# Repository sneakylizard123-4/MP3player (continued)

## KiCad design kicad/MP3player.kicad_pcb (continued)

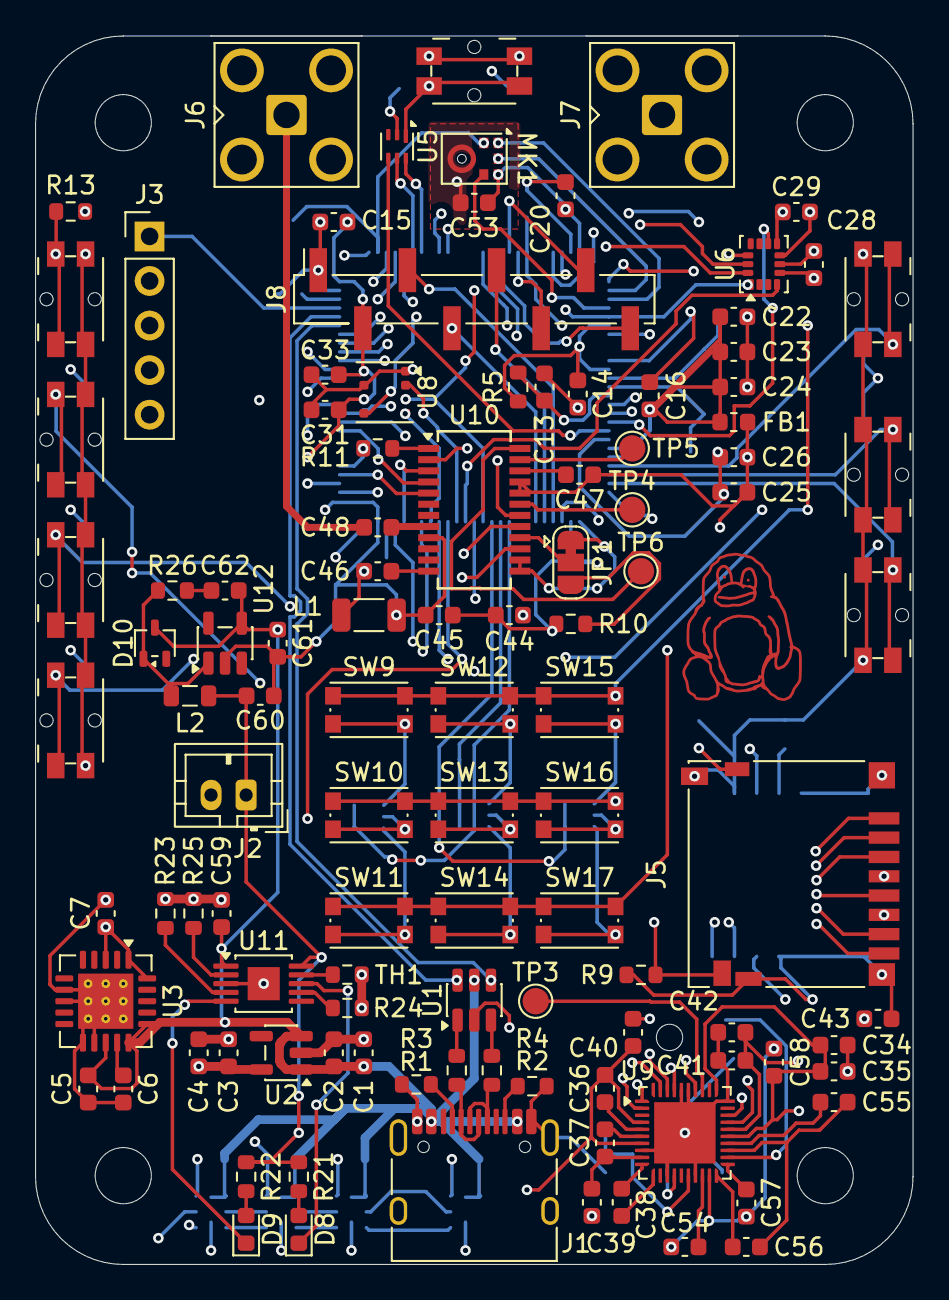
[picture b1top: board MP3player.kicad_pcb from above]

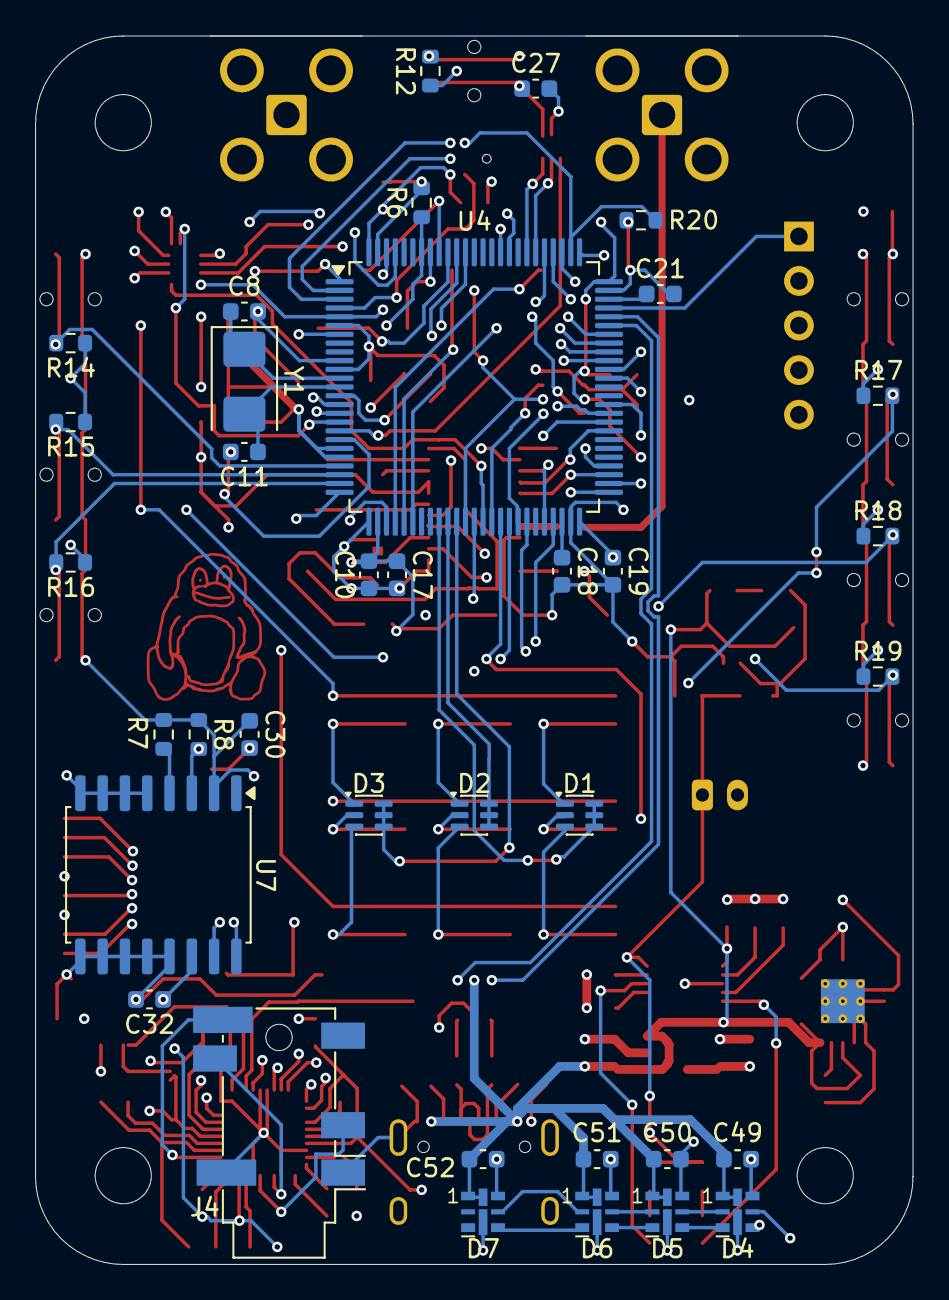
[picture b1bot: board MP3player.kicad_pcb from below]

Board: 6 copper layers, 50.0 x 70.0 mm, 148 parts (36 on the bottom side), 136 nets.

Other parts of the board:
C59: 1uF; C_0603_1608Metric
C60: 4.7uF; C_0603_1608Metric
C61: 22uF; C_0603_1608Metric
C62: 120pF; C_0603_1608Metric
D8, D9: LED; LED_0603_1608Metric
D10: BAT54W; SOT-323_SC-70
L2: 2.2uH; L_0805_2012Metric
R21, R22: 1.5k; R_0603_1608Metric
R23, R25: 1.1k; R_0603_1608Metric
R24: 11k; R_0603_1608Metric
R26: 5.11R; R_0603_1608Metric
TH1: 10k; R_0603_1608Metric
U11: BQ24090DGQ; HVSSOP-10-1EP_3x3mm_P0.5mm_EP1.83x1.89mm
U12: TPS613222ADBV; SOT-23-5

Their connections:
+5V: C59.1, C61.1, C62.2, D10.3 (K), U11.1 (IN), U12.4 (VOUT); also elsewhere on the board
+BATT: C60.1, L2.1, R21.1, R22.1, U11.10 (OUT); also elsewhere on the board
GND: C59.2, C60.2, C61.2, R23.2, R24.2, R25.2, TH1.2, U11.3 (VSS), U11.11 (VSS), U12.2 (GND); also elsewhere on the board
unnamed: C62.1, R26.2
unnamed: D8.2 (A), R21.2
unnamed: D8.1 (K), U11.8 (~CHG)
unnamed: D9.2 (A), R22.2
unnamed: D9.1 (K), U11.5 (~PG)
unnamed: D10.1 (A), L2.2, R26.1, U12.1 (SW)
unnamed: R24.1, U11.7 (ISET2)
unnamed: R25.1, U11.2 (ISET)
unnamed: R23.1, U11.4 (PRETERM)
unnamed: TH1.1, U11.9 (TS)

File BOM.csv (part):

Refs,Value,Footprint,Qty,LCSC#,MPN,Manufacturer,Unit Price($),Product Link
C1,10uF,Capacitor_SMD:C_0603_1608Metric,1,C19702,CL10A106KP8NNNC,Samsung Electro-Mechanics,0.0390,https://www.lcsc.com/product-detail/C19702.html
C2,1uF,Capacitor_SMD:C_0603_1608Metric,1,C29936,CL10B105KA8NNNC,Samsung Electro-Mechanics,0.0229,https://www.lcsc.com/product-detail/C29936.html
C3,10uF,Capacitor_SMD:C_0603_1608Metric,1,C19702,CL10A106KP8NNNC,Samsung Electro-Mechanics,0.0390,https://www.lcsc.com/product-detail/C19702.html
C4,1uF,Capacitor_SMD:C_0603_1608Metric,1,C29936,CL10B105KA8NNNC,Samsung Electro-Mechanics,0.0229,https://www.lcsc.com/product-detail/C29936.html
C5,10uF,Capacitor_SMD:C_0603_1608Metric,1,C19702,CL10A106KP8NNNC,Samsung Electro-Mechanics,0.0390,https://www.lcsc.com/product-detail/C19702.html
C6,1uF,Capacitor_SMD:C_0603_1608Metric,1,C29936,CL10B105KA8NNNC,Samsung Electro-Mechanics,0.0229,https://www.lcsc.com/product-detail/C29936.html
C7,47uF,Capacitor_SMD:C_0603_1608Metric,1,C140782,GRM188R60J476ME15D,muRata,0.2397,https://www.lcsc.com/product-detail/C140782.html
C8,12pF,Capacitor_SMD:C_0603_1608Metric,1,C107034,CC0603JRNPO9BN120,YAGEO,0.0090,https://www.lcsc.com/product-detail/C107034.html
C10,0.1uF,Capacitor_SMD:C_0603_1608Metric,1,C1591,CL10B104KB8NNNC,Samsung Electro-Mechanics,0.0160,https://www.lcsc.com/product-detail/C1591.html
C11,12pF,Capacitor_SMD:C_0603_1608Metric,1,C107034,CC0603JRNPO9BN120,YAGEO,0.0090,https://www.lcsc.com/product-detail/C107034.html
C13,100nF,Capacitor_SMD:C_0603_1608Metric,1,C1591,CL10B104KB8NNNC,Samsung Electro-Mechanics,0.0160,https://www.lcsc.com/product-detail/C1591.html
C14,0.1uF,Capacitor_SMD:C_0603_1608Metric,1,C1591,CL10B104KB8NNNC,Samsung Electro-Mechanics,0.0160,https://www.lcsc.com/product-detail/C1591.html
C15,0.1uF,Capacitor_SMD:C_0603_1608Metric,1,C1591,CL10B104KB8NNNC,Samsung Electro-Mechanics,0.0160,https://www.lcsc.com/product-detail/C1591.html
C16,100nF,Capacitor_SMD:C_0603_1608Metric,1,C1591,CL10B104KB8NNNC,Samsung Electro-Mechanics,0.0160,https://www.lcsc.com/product-detail/C1591.html
C17,0.1uF,Capacitor_SMD:C_0603_1608Metric,1,C1591,CL10B104KB8NNNC,Samsung Electro-Mechanics,0.0160,https://www.lcsc.com/product-detail/C1591.html
C18,2.2uF,Capacitor_SMD:C_0603_1608Metric,1,C23630,CL10A225KO8NNNC,Samsung Electro-Mechanics,0.0289,https://www.lcsc.com/product-detail/C23630.html
C19,100nF,Capacitor_SMD:C_0603_1608Metric,1,C1591,CL10B104KB8NNNC,Samsung Electro-Mechanics,0.0160,https://www.lcsc.com/product-detail/C1591.html
C20,0.1uF,Capacitor_SMD:C_0603_1608Metric,1,C1591,CL10B104KB8NNNC,Samsung Electro-Mechanics,0.0160,https://www.lcsc.com/product-detail/C1591.html
C21,2.2uF,Capacitor_SMD:C_0603_1608Metric,1,C23630,CL10A225KO8NNNC,Samsung Electro-Mechanics,0.0289,https://www.lcsc.com/product-detail/C23630.html
C22,10nF,Capacitor_SMD:C_0603_1608Metric,1,C100042,CC0603KRX7R9BB103,YAGEO,0.0160,https://www.lcsc.com/product-detail/C100042.html
C23,100nF,Capacitor_SMD:C_0603_1608Metric,1,C1591,CL10B104KB8NNNC,Samsung Electro-Mechanics,0.0160,https://www.lcsc.com/product-detail/C1591.html
C24,1uF,Capacitor_SMD:C_0603_1608Metric,1,C29936,CL10B105KA8NNNC,Samsung Electro-Mechanics,0.0229,https://www.lcsc.com/product-detail/C29936.html
C25,1uF,Capacitor_SMD:C_0603_1608Metric,1,C29936,CL10B105KA8NNNC,Samsung Electro-Mechanics,0.0229,https://www.lcsc.com/product-detail/C29936.html
C26,100nF,Capacitor_SMD:C_0603_1608Metric,1,C1591,CL10B104KB8NNNC,Samsung Electro-Mechanics,0.0160,https://www.lcsc.com/product-detail/C1591.html
C27,100nF,Capacitor_SMD:C_0603_1608Metric,1,C1591,CL10B104KB8NNNC,Samsung Electro-Mechanics,0.0160,https://www.lcsc.com/product-detail/C1591.html
C28,100nF,Capacitor_SMD:C_0603_1608Metric,1,C1591,CL10B104KB8NNNC,Samsung Electro-Mechanics,0.0160,https://www.lcsc.com/product-detail/C1591.html
C29,100nF,Capacitor_SMD:C_0603_1608Metric,1,C1591,CL10B104KB8NNNC,Samsung Electro-Mechanics,0.0160,https://www.lcsc.com/product-detail/C1591.html
C30,100nF,Capacitor_SMD:C_0603_1608Metric,1,C1591,CL10B104KB8NNNC,Samsung Electro-Mechanics,0.0160,https://www.lcsc.com/product-detail/C1591.html
C31,100nF,Capacitor_SMD:C_0603_1608Metric,1,C1591,CL10B104KB8NNNC,Samsung Electro-Mechanics,0.0160,https://www.lcsc.com/product-detail/C1591.html
C32,100nF,Capacitor_SMD:C_0603_1608Metric,1,C1591,CL10B104KB8NNNC,Samsung Electro-Mechanics,0.0160,https://www.lcsc.com/product-detail/C1591.html
C33,100nF,Capacitor_SMD:C_0603_1608Metric,1,C1591,CL10B104KB8NNNC,Samsung Electro-Mechanics,0.0160,https://www.lcsc.com/product-detail/C1591.html
C34,100nF,Capacitor_SMD:C_0603_1608Metric,1,C1591,CL10B104KB8NNNC,Samsung Electro-Mechanics,0.0160,https://www.lcsc.com/product-detail/C1591.html
C35,100nF,Capacitor_SMD:C_0603_1608Metric,1,C1591,CL10B104KB8NNNC,Samsung Electro-Mechanics,0.0160,https://www.lcsc.com/product-detail/C1591.html
C36,15uF,Capacitor_SMD:C_0603_1608Metric,1,C445715,C1608X5R0J156MT000E,TDK,0.1322,https://www.lcsc.com/product-detail/C445715.html
C37,15uF,Capacitor_SMD:C_0603_1608Metric,1,C445715,C1608X5R0J156MT000E,TDK,0.1322,https://www.lcsc.com/product-detail/C445715.html
C38,2.2uF,Capacitor_SMD:C_0603_1608Metric,1,C23630,CL10A225KO8NNNC,Samsung Electro-Mechanics,0.0289,https://www.lcsc.com/product-detail/C23630.html
C39,2.2uF,Capacitor_SMD:C_0603_1608Metric,1,C23630,CL10A225KO8NNNC,Samsung Electro-Mechanics,0.0289,https://www.lcsc.com/product-detail/C23630.html
C40,2.2uF,Capacitor_SMD:C_0603_1608Metric,1,C23630,CL10A225KO8NNNC,Samsung Electro-Mechanics,0.0289,https://www.lcsc.com/product-detail/C23630.html
C41,100nF,Capacitor_SMD:C_0603_1608Metric,1,C1591,CL10B104KB8NNNC,Samsung Electro-Mechanics,0.0160,https://www.lcsc.com/product-detail/C1591.html
C42,4.7uF,Capacitor_SMD:C_0603_1608Metric,1,C19666,CL10A475KO8NNNC,Samsung Electro-Mechanics,0.0339,https://www.lcsc.com/product-detail/C19666.html
C43,100nF,Capacitor_SMD:C_0603_1608Metric,1,C1591,CL10B104KB8NNNC,Samsung Electro-Mechanics,0.0160,https://www.lcsc.com/product-detail/C1591.html
C44,0.1uF,Capacitor_SMD:C_0603_1608Metric,1,C1591,CL10B104KB8NNNC,Samsung Electro-Mechanics,0.0160,https://www.lcsc.com/product-detail/C1591.html
C45,0.1uF,Capacitor_SMD:C_0603_1608Metric,1,C1591,CL10B104KB8NNNC,Samsung Electro-Mechanics,0.0160,https://www.lcsc.com/product-detail/C1591.html
C46,1nF,Capacitor_SMD:C_0603_1608Metric,1,C100040,CC0603KRX7R9BB102,YAGEO,0.0152,https://www.lcsc.com/product-detail/C100040.html
C47,22nF,Capacitor_SMD:C_0603_1608Metric,1,C21122,CL10B223KB8NNNC,Samsung Electro-Mechanics,0.0151,https://www.lcsc.com/product-detail/C21122.html
C48,1nF,Capacitor_SMD:C_0603_1608Metric,1,C100040,CC0603KRX7R9BB102,YAGEO,0.0152,https://www.lcsc.com/product-detail/C100040.html
C49,0.1uF,Capacitor_SMD:C_0603_1608Metric,1,C1591,CL10B104KB8NNNC,Samsung Electro-Mechanics,0.0160,https://www.lcsc.com/product-detail/C1591.html
C50,0.1uF,Capacitor_SMD:C_0603_1608Metric,1,C1591,CL10B104KB8NNNC,Samsung Electro-Mechanics,0.0160,https://www.lcsc.com/product-detail/C1591.html
C51,0.1uF,Capacitor_SMD:C_0603_1608Metric,1,C1591,CL10B104KB8NNNC,Samsung Electro-Mechanics,0.0160,https://www.lcsc.com/product-detail/C1591.html
C52,0.1uF,Capacitor_SMD:C_0603_1608Metric,1,C1591,CL10B104KB8NNNC,Samsung Electro-Mechanics,0.0160,https://www.lcsc.com/product-detail/C1591.html
C53,100nF,Capacitor_SMD:C_0603_1608Metric,1,C1591,CL10B104KB8NNNC,Samsung Electro-Mechanics,0.0160,https://www.lcsc.com/product-detail/C1591.html
C54,2.2uF,Capacitor_SMD:C_0603_1608Metric,1,C23630,CL10A225KO8NNNC,Samsung Electro-Mechanics,0.0289,https://www.lcsc.com/product-detail/C23630.html
C55,2.2uF,Capacitor_SMD:C_0603_1608Metric,1,C23630,CL10A225KO8NNNC,Samsung Electro-Mechanics,0.0289,https://www.lcsc.com/product-detail/C23630.html
C56,2.2uF,Capacitor_SMD:C_0603_1608Metric,1,C23630,CL10A225KO8NNNC,Samsung Electro-Mechanics,0.0289,https://www.lcsc.com/product-detail/C23630.html
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
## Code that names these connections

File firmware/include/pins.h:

#pragma once

#include "stm32h7xx_hal.h"

// ─── Buttons (direct GPIO, active low) ─────────────────────────────
#define BTN_POWER_Pin       GPIO_PIN_0
#define BTN_POWER_Port      GPIOA
#define BTN_VOL_UP_Pin      GPIO_PIN_1
#define BTN_VOL_UP_Port     GPIOA
#define BTN_VOL_DOWN_Pin    GPIO_PIN_2
#define BTN_VOL_DOWN_Port   GPIOA
#define BTN_LOCK_Pin        GPIO_PIN_3
#define BTN_LOCK_Port       GPIOA
#define BTN_RECORD_Pin      GPIO_PIN_4
#define BTN_RECORD_Port     GPIOA
#define BTN_USER_Pin        GPIO_PIN_1
#define BTN_USER_Port       GPIOC
#define BTN_BOOT0_Pin       GPIO_PIN_0
#define BTN_BOOT0_Port      GPIOC

// ─── Button Matrix ─────────────────────────────────────────────────
#define BTN_MATRIX_ROW1_Pin GPIO_PIN_3
#define BTN_MATRIX_ROW1_Port GPIOB
#define BTN_MATRIX_ROW2_Pin GPIO_PIN_4
#define BTN_MATRIX_ROW2_Port GPIOB
#define BTN_MATRIX_ROW3_Pin GPIO_PIN_0
#define BTN_MATRIX_ROW3_Port GPIOC
#define BTN_MATRIX_COL1_Pin GPIO_PIN_0
#define BTN_MATRIX_COL1_Port GPIOB
#define BTN_MATRIX_COL2_Pin GPIO_PIN_1
#define BTN_MATRIX_COL2_Port GPIOB
#define BTN_MATRIX_COL3_Pin GPIO_PIN_2
#define BTN_MATRIX_COL3_Port GPIOB

// ─── OLED Display (SPI) ───────────────────────────────────────────
#define OLED_SCK_Pin        GPIO_PIN_5
#define OLED_SCK_Port       GPIOA
#define OLED_MOSI_Pin       GPIO_PIN_7
#define OLED_MOSI_Port      GPIOA
#define OLED_CS_Pin         GPIO_PIN_6
#define OLED_CS_Port        GPIOB
#define OLED_DC_Pin         GPIO_PIN_7
#define OLED_DC_Port        GPIOB
#define OLED_RST_Pin        GPIO_PIN_6
#define OLED_RST_Port       GPIOA
#define OLED_BL_Pin         GPIO_PIN_5
#define OLED_BL_Port        GPIOB

// ─── I2S Audio (CS43131 DAC) ───────────────────────────────────────
#define I2S_MCLK_Pin        GPIO_PIN_1
#define I2S_MCLK_Port       GPIOE
#define I2S_SDOUT_Pin       GPIO_PIN_14
#define I2S_SDOUT_Port      GPIOE
#define I2S_BCLK_Pin        GPIO_PIN_12
#define I2S_BCLK_Port       GPIOE
#define I2S_LRCLK_Pin       GPIO_PIN_11
#define I2S_LRCLK_Port      GPIOE
#define AUDIO_RESET_Pin     GPIO_PIN_4
#define AUDIO_RESET_Port    GPIOD
#define AUDIO_INT_Pin       GPIO_PIN_3
#define AUDIO_INT_Port      GPIOD

// ─── I2C: Audio DAC control ────────────────────────────────────────
#define AUDIO_SCL_Pin       GPIO_PIN_1
#define AUDIO_SCL_Port      GPIOE
#define AUDIO_SDA_Pin       GPIO_PIN_0
#define AUDIO_SDA_Port      GPIOE

// ─── I2C: Sensors (LSM6DSL, ISL29035, BME680) ────────────────────
#define SENSORS_I2C_SCL_Pin  GPIO_PIN_0
#define SENSORS_I2C_SCL_Port GPIOD
#define SENSORS_I2C_SDA_Pin  GPIO_PIN_1
#define SENSORS_I2C_SDA_Port GPIOD

// ─── SPI: Sensors (LSM6DSL, BME680) ───────────────────────────────
#define SENSORS_SPI_SCK_Pin  GPIO_PIN_13
#define SENSORS_SPI_SCK_Port GPIOE
#define SENSORS_SPI_MISO_Pin GPIO_PIN_5
#define SENSORS_SPI_MISO_Port GPIOE
#define SENSORS_SPI_MOSI_Pin GPIO_PIN_6
#define SENSORS_SPI_MOSI_Port GPIOE
#define IMU_CS_Pin           GPIO_PIN_8
#define IMU_CS_Port          GPIOE
#define GAS_CS_Pin           GPIO_PIN_10
#define GAS_CS_Port          GPIOE
#define IMU_INT1_Pin         GPIO_PIN_9
#define IMU_INT1_Port        GPIOE
#define IMU_INT2_Pin         GPIO_PIN_2
#define IMU_INT2_Port        GPIOC
#define LIGHT_INT_Pin        GPIO_PIN_3
#define LIGHT_INT_Port       GPIOC

// ─── I2S: Microphone (ICS-43434) ──────────────────────────────────
#define MIC_DATA_Pin        GPIO_PIN_2
#define MIC_DATA_Port       GPIOE
#define MIC_LRCLK_Pin       GPIO_PIN_3
#define MIC_LRCLK_Port      GPIOE
#define MIC_BCLK_Pin        GPIO_PIN_4
#define MIC_BCLK_Port       GPIOE
#define MIC_CHANNEL_Pin     GPIO_PIN_15
#define MIC_CHANNEL_Port    GPIOA

// ─── I2S: Radio (Si4735) ──────────────────────────────────────────
#define RADIO_I2S_BCLK_Pin  GPIO_PIN_10
#define RADIO_I2S_BCLK_Port GPIOB
#define RADIO_I2S_LRCLK_Pin GPIO_PIN_12
#define RADIO_I2S_LRCLK_Port GPIOB
#define RADIO_I2S_DATA_Pin  GPIO_PIN_15
#define RADIO_I2S_DATA_Port GPIOB
#define RADIO_SCL_Pin       GPIO_PIN_12
#define RADIO_SCL_Port      GPIOD
#define RADIO_SDA_Pin       GPIO_PIN_13
#define RADIO_SDA_Port      GPIOD
#define RADIO_RST_Pin       GPIO_PIN_14
#define RADIO_RST_Port      GPIOD
#define RADIO_IRQ_Pin       GPIO_PIN_11
#define RADIO_IRQ_Port      GPIOD
#define RADIO_GP1_Pin       GPIO_PIN_14
#define RADIO_GP1_Port      GPIOB

// ─── LED Strip (APA102) ───────────────────────────────────────────
#define LED_SCK_Pin         GPIO_PIN_11
#define LED_SCK_Port        GPIOB
#define LED_MOSI_Pin        GPIO_PIN_13
#define LED_MOSI_Port       GPIOB

// ─── SD Card (SDMMC) ──────────────────────────────────────────────
#define SDMMC_CLK_Pin       GPIO_PIN_12
#define SDMMC_CLK_Port      GPIOC
#define SDMMC_CMD_Pin       GPIO_PIN_13
#define SDMMC_CMD_Port      GPIOC
#define SDMMC_D0_Pin        GPIO_PIN_8
#define SDMMC_D0_Port       GPIOC
#define SDMMC_D1_Pin        GPIO_PIN_9
#define SDMMC_D1_Port       GPIOC
#define SDMMC_D2_Pin        GPIO_PIN_10
#define SDMMC_D2_Port       GPIOC
#define SDMMC_D3_Pin        GPIO_PIN_11
#define SDMMC_D3_Port       GPIOC
#define SDMMC_DET_Pin       GPIO_PIN_7
#define SDMMC_DET_Port      GPIOC

// ─── USB ───────────────────────────────────────────────────────────
#define USB_DM_Pin          GPIO_PIN_11
#define USB_DM_Port         GPIOA
#define USB_DP_Pin          GPIO_PIN_12
#define USB_DP_Port         GPIOA

// ─── RTC (DS3231M) ────────────────────────────────────────────────
#define RTC_SCL_Pin         GPIO_PIN_8
#define RTC_SCL_Port        GPIOA
#define RTC_SDA_Pin         GPIO_PIN_9
#define RTC_SDA_Port        GPIOA
#define RTC_INT_Pin         GPIO_PIN_10
#define RTC_INT_Port        GPIOA

// ─── Power Management (PMM) ───────────────────────────────────────
#define PMM_TX_Pin          GPIO_PIN_8
#define PMM_TX_Port         GPIOD
#define PMM_RX_Pin          GPIO_PIN_9
#define PMM_RX_Port         GPIOD
#define PMM_SHDN_Pin        GPIO_PIN_10
#define PMM_SHDN_Port       GPIOD
#define PMM_FORCE_Pin       GPIO_PIN_7
#define PMM_FORCE_Port      GPIOD
#define PMM_INIT_Pin        GPIO_PIN_15
#define PMM_INIT_Port       GPIOD
#define PWR_I2C_SCL_Pin     GPIO_PIN_8
#define PWR_I2C_SCL_Port    GPIOB
#define PWR_I2C_SDA_Pin     GPIO_PIN_9
#define PWR_I2C_SDA_Port    GPIOB

// ─── Debug (SWD) ──────────────────────────────────────────────────
#define SWDIO_Pin           GPIO_PIN_13
#define SWDIO_Port          GPIOA
#define SWCLK_Pin           GPIO_PIN_14
#define SWCLK_Port          GPIOA
